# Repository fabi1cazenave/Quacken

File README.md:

# Quacken

Libre, ergonomic, *polymorphic*: a single PCB for many possible layouts
— 3×6, 3×5, hummingbird, and everything in between.

## Roadmap

- [x] **Quacken Zero**: unibody
  - [x] first batch with a ProMicro slot, to validate the geometry and design choices
  - [ ] next batches with an onboard nRF52840 (Bluetooth)

- [ ] **Quacken Split**: unibody by default, splittable by choice
  - [ ] onboard RP2040 (left) and I/O expander (right)
  - [ ] splittable in two (I³C communication over a TRRS cable)
  - [ ] splittable outer columns
  - [ ] hotswap sockets
  - [ ] optional Circle Trackpad
  - [ ] optional rotary encoders

- [ ] **Marie-Quackenette*: split and wireless variant of the Quacken Split.

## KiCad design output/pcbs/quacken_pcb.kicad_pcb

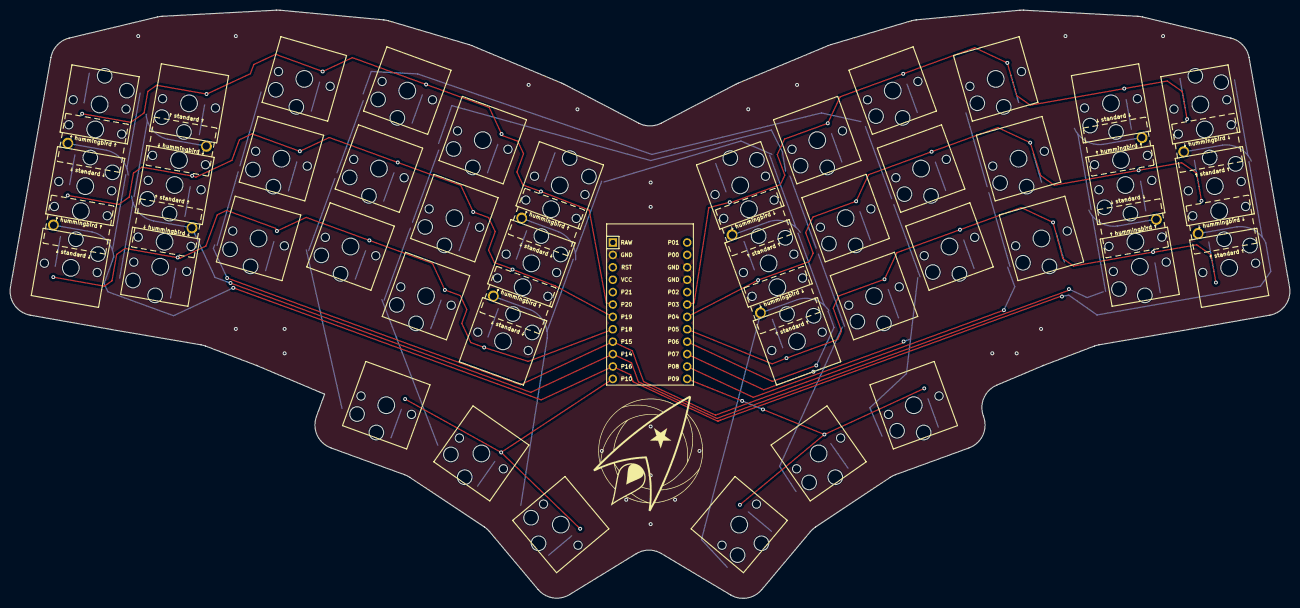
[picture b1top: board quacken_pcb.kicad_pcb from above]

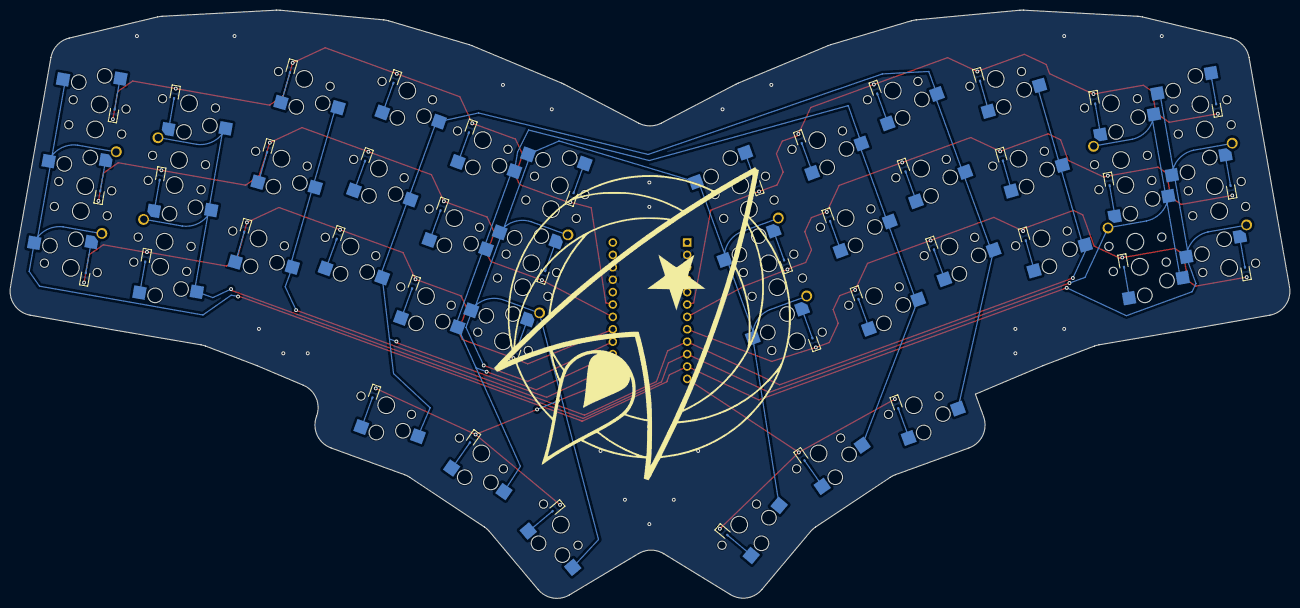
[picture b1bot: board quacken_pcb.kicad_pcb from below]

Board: 2 copper layers, 262.2 x 120.5 mm, 85 parts (42 on the bottom side), 57 nets.

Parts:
D1, D2, D3, D4, D5, D6, D7, D8, D9, D10, D11, D12, D13, D14, D15, D16, D17, D18, D19, D20, D21, D22, D23, D24, D25, D26, D27, D28, D29, D30, D31, D32, D33, D34, D35, D36, D37, D38, D39, D40, D41, D42: D_SOD-323
MCU1: ProMicro
S1, S2, S3, S4, S5, S6, S7, S8, S9, S10, S11, S12, S13, S14, S15, S16, S17, S18, S19, S20, S21, S22, S23, S24, S25, S26, S27, S28, S29, S30, S31, S32, S33, S34, S35, S36, S37, S38, S39, S40, S41, S42: PG1350

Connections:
GND: MCU1.2, MCU1.15, MCU1.16
P3: D18.1, D21.1, D24.1, D27.1, D39.1, D42.1, MCU1.18
P4: D17.1, D20.1, D23.1, D26.1, D38.1, D41.1, MCU1.19
P5: D16.1, D19.1, D22.1, D25.1, D37.1, D40.1, MCU1.20
P6: MCU1.21, S15.2, S30.2, S34.2, S34.3, S35.2, S35.3, S36.2, S40.2, S40.3, S41.2, S41.3, S42.2
P7: MCU1.22, S10.2, S11.2, S12.2, S14.2, S25.2, S26.2, S27.2, S29.2
P8: MCU1.23, S7.2, S8.2, S9.2, S13.2, S22.2, S23.2, S24.2, S28.2
P9: D28.1, D29.1, D30.1, MCU1.24
P10: D13.1, D14.1, D15.1, MCU1.12
P14: MCU1.10, S1.2, S2.2, S2.3, S3.2, S3.3, S16.2, S17.2, S17.3, S18.2, S18.3
P15: MCU1.9, S4.2, S5.2, S6.2, S19.2, S20.2, S21.2
P16: MCU1.11, S31.2, S31.3, S32.2, S32.3, S33.2, S37.2, S37.3, S38.2, S38.3, S39.2
P18: D1.1, D4.1, D7.1, D10.1, D31.1, D34.1, MCU1.8
P19: D2.1, D5.1, D8.1, D11.1, D32.1, D35.1, MCU1.7
P20: D3.1, D6.1, D9.1, D12.1, D33.1, D36.1, MCU1.6
comfy_default: D14.2, S14.1
index_bottom: D10.2, S10.1
index_home: D11.2, S11.1
index_top: D12.2, S12.1
inner_bottom: D34.2, S34.1
inner_home: D35.2, S35.1
inner_top: D36.2, S36.1
middle_bottom: D7.2, S7.1
middle_home: D8.2, S8.1
middle_top: D9.2, S9.1
mirror_comfy_default: D29.2, S29.1
mirror_index_bottom: D25.2, S25.1
mirror_index_home: D26.2, S26.1
mirror_index_top: D27.2, S27.1
mirror_inner_bottom: D40.2, S40.1
mirror_inner_home: D41.2, S41.1
mirror_inner_top: D42.2, S42.1
mirror_middle_bottom: D22.2, S22.1
mirror_middle_home: D23.2, S23.1
mirror_middle_top: D24.2, S24.1
mirror_outer_bottom: D37.2, S37.1
mirror_outer_home: D38.2, S38.1
mirror_outer_top: D39.2, S39.1
mirror_pinky_bottom: D16.2, S16.1
mirror_pinky_home: D17.2, S17.1
mirror_pinky_top: D18.2, S18.1
mirror_reachy_default: D30.2, S30.1
mirror_ring_bottom: D19.2, S19.1
mirror_ring_home: D20.2, S20.1
mirror_ring_top: D21.2, S21.1
mirror_tucky_default: D28.2, S28.1
outer_bottom: D31.2, S31.1
outer_home: D32.2, S32.1
outer_top: D33.2, S33.1
pinky_bottom: D1.2, S1.1
pinky_home: D2.2, S2.1
pinky_top: D3.2, S3.1
reachy_default: D15.2, S15.1
ring_bottom: D4.2, S4.1
ring_home: D5.2, S5.1
ring_top: D6.2, S6.1
tucky_default: D13.2, S13.1

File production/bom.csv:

Designator,Footprint,Quantity,Value,LCSC Part #
"D1, D10, D11, D12, D13, D14, D15, D16, D17, D18, D19, D2, D20, D21, D22, D23, D24, D25, D26, D27, D28, D29, D3, D30, D31, D32, D33, D34, D35, D36, D37, D38, D39, D4, D40, D41, D42, D5, D6, D7, D8, D9",D_SOD-323,42,,
"S1, S10, S11, S12, S13, S14, S15, S16, S17, S18, S19, S2, S20, S21, S22, S23, S24, S25, S26, S27, S28, S29, S3, S30, S31, S32, S33, S34, S35, S36, S37, S38, S39, S4, S40, S41, S42, S5, S6, S7, S8, S9",PG1350,42,,

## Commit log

2025-06-13 Initial commit: semi-minimalist keyboard.
2025-06-15 Added gerbers archive.
2025-06-23 Put capacitors on bottom side + better hotswap.
2025-06-23 Reorganised repo.
2025-06-27 First batch of Quacken Zero!
2025-06-27 Added LICENSE
2025-07-12 Add pcb images
    To actually see what we are talking about
2025-07-21 quick SVG mock-up (with magic numbers)
2025-07-22 gémétrie calquée sur Ergogen
2025-07-22 deux piafs de plus
2025-07-23 page web + selecteur
2025-07-23 typos
2025-07-23 Align geometry on KiCad outputs
2025-07-23 formatting
2025-07-23 style and size
2025-07-23 mobile-friendlier
2025-07-24 simpler color theme
2025-07-24 quick SVG mock-up (with magic numbers) (#2)
    * quick SVG mock-up (with magic numbers)
    * gémétrie calquée sur Ergogen
    * deux piafs de plus
    * page web + selecteur
    * typos
    * Align geometry on KiCad outputs
2025-07-24 better SVG viewbox
2025-07-29 separate keys: median, fixed, thumbs
2025-08-12 keyberon firmware (#3)
    * (wip) keyberon firmware
    * credentials
    * Updated `.gitignore` file.
    * credentials
    * Fixed compilation errors related to usb.
    * wip: switch to the latest rp2040_hal API
